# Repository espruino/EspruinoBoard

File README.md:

EspruinoBoard
============

Espruino Hardware Schematics

This repository contains the hardware schematics for the Espruino Boards.

* [Original Espruino Board](http://www.espruino.com/EspruinoBoard) - [see schematics](Original)
* [Espruino Pico Board](http://www.espruino.com/Pico) - [see schematics](Pico)
* [Espruino WiFi Board](http://www.espruino.com/WiFi) - [see schematics](WiFi)
* [Puck.js Board](http://www.espruino.com/Puck.js) - [see schematics](Puck.js)
* [Pixl.js Board](http://www.espruino.com/Pixl.js) - [see schematics](Pixl.js)
* [MDBT42Q Breakout Board](http://www.espruino.com/MDBT42Q) and Eagle Library - [see schematics](MDBT42)

If you want to buy pre-made boards [please support us by buying from here](http://www.espruino.com/Order)

* [Boxes for Espruino Boards](boxes)
* [Fritzing part library](frizting)
* [Bangle.js related parts](Bangle.js)

See the [LICENSE](LICENSE) file for details of the license in this repository.

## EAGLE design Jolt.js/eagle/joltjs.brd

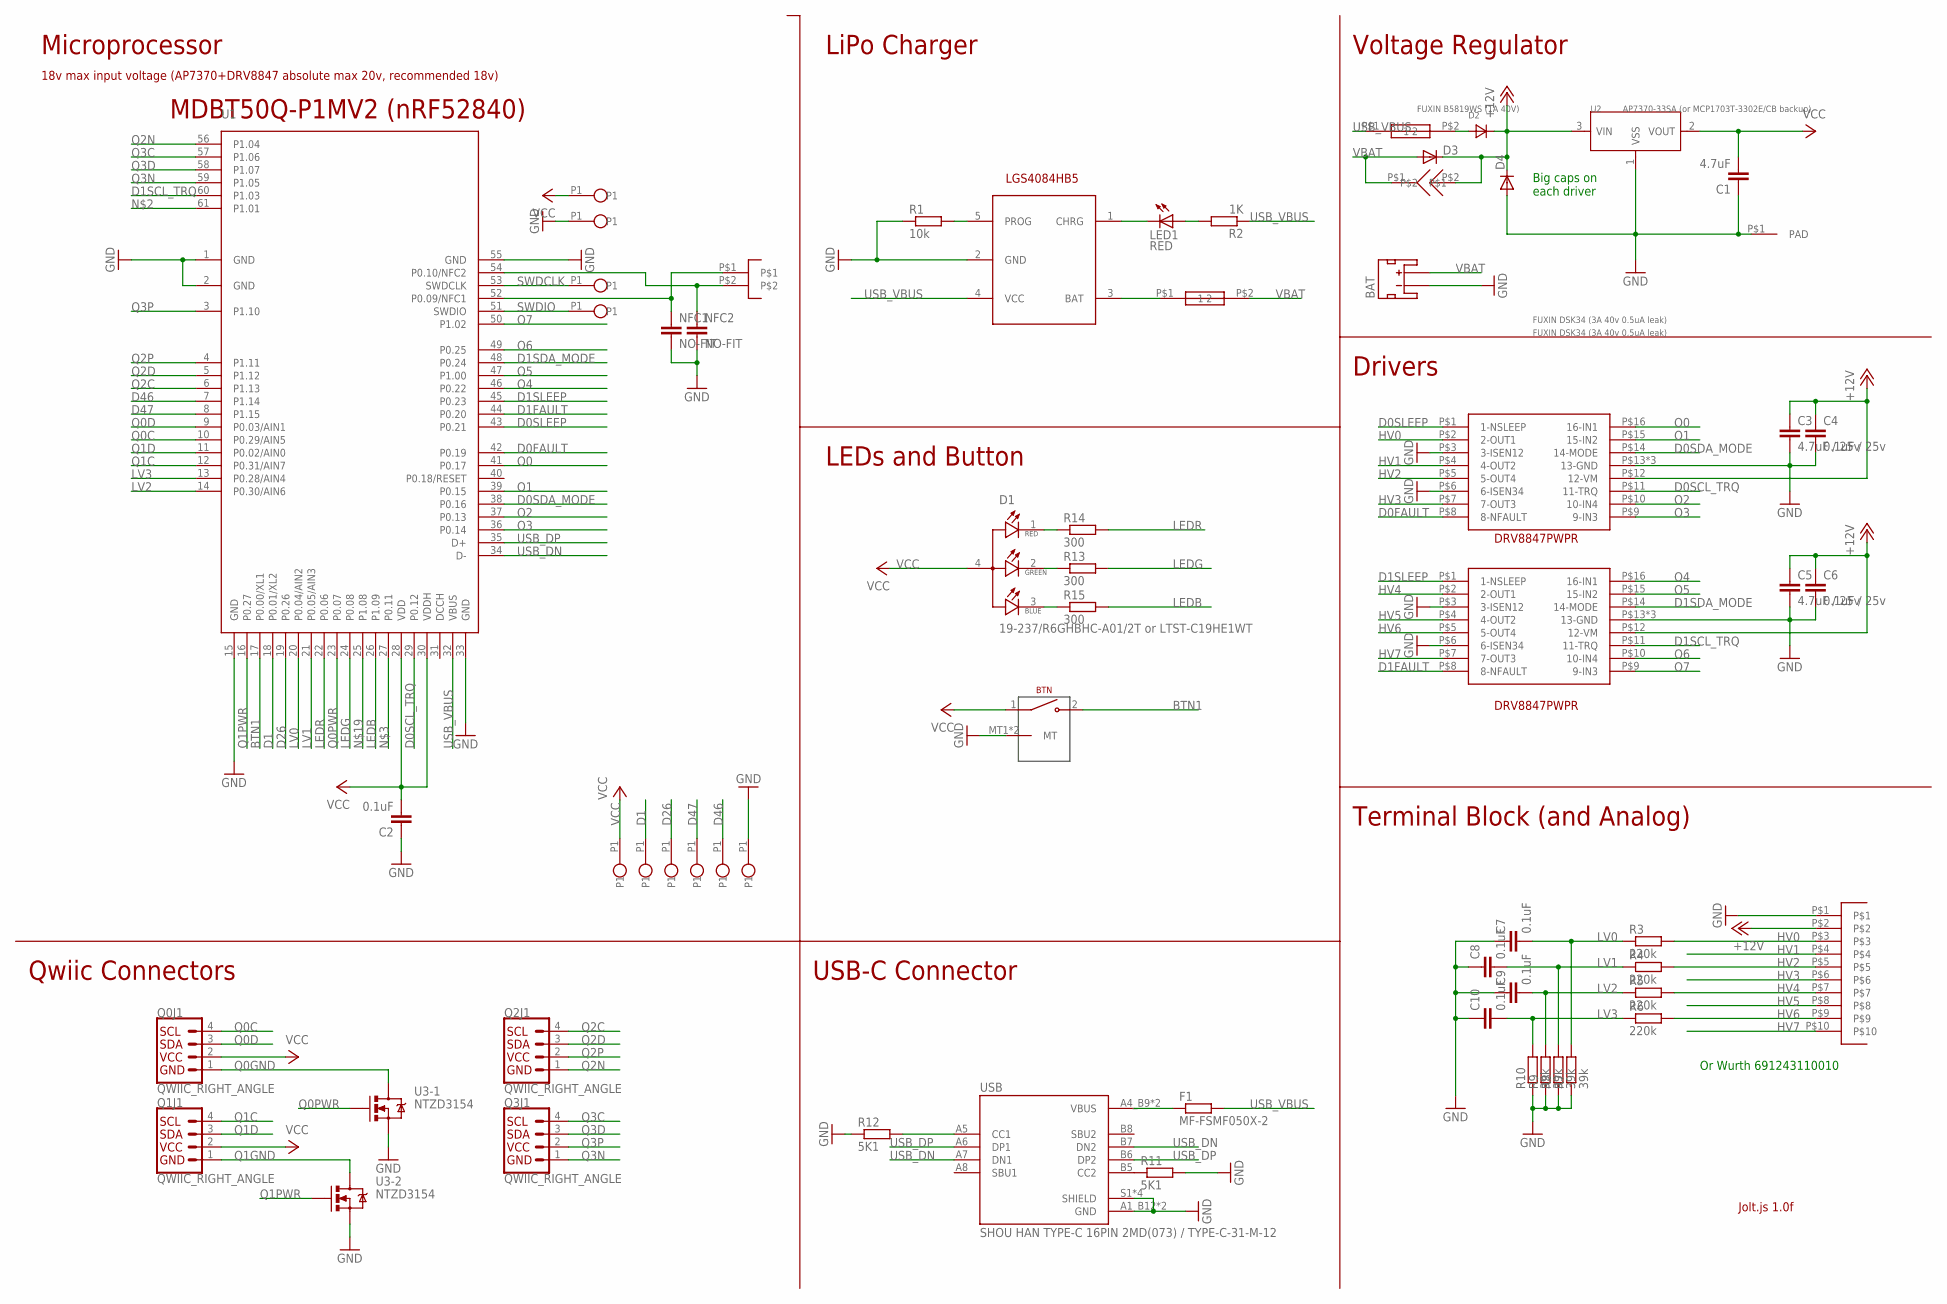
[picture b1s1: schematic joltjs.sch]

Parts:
BAT: C47647 / S2B-PH-SM4-TB; JST-2-SMD
BTN: GT-TC054C; TACT_MEDI_RIGHT_ANGLE
C1: 4.7uF; C0805
C2, C7, C8, C9, C10: 0.1uF; C0603
C3, C5: 4.7uF / 25v; C0805
C4, C6: 0.1uF / 25v; C0603
D1: 19-237/R6GHBHC-A01/2T or LTST-C19HE1WT; LED_19-237/R6GHBHC-A01/2T
D2: FUXIN B5819WS (1A 40V); SOD323
D3, D4: FUXIN DSK34 (3A 40v 0.5uA leak); SOD-123_MINI-SMA
F1: MF-FSMF050X-2; R0603
JUMPER_LIPO_CHG: NO-FIT; WIRELINK2
JUMPER_LIPO_PWR: NO-FIT; SOLDERJUMPER
JUMPER_USB_PWR: NO-FIT; WIRELINK2
LED1: RED; CHIPLED_0603
NFC: PINHEAD-1.27-2X1
NFC1, NFC2: NO-FIT; C0603
Q0, Q1, Q2, Q3: QWIIC_RIGHT_ANGLE; JST04_1MM_RA
R1: 10k; R0603
R2: 1K; R0603
R3, R4, R5, R6: 220k; R0603
R7, R8, R9, R10: 39k; R0603
R11, R12: 5K1; R0603
R13, R14, R15: 300; R0603
SCREWHOLE: MOUNT-M3
SWCK, SWCK2: NO-FIT; SINGLE
SWD: NO-FIT; SINGLE
U1: MDBT50Q-P1MV2; MDBT50
U2: AP7370-33SA (or MCP1703T-3302E/CB backup); SOT23A
U3: NTZD3154; SOT563
U4: LGS4084HB5; SOT23-5
U$5: DORABO DB125-3.5-10P-GN-S; DB125-3.5-XXP
UD1, UD2: DRV8847PWPR
USB: SHOU HAN TYPE-C 16PIN 2MD(073) / TYPE-C-31-M-12; HRO_TYPE-C-31-M-12
VCC, VCC1, VCC2, VCC3, VCC4, VCC5, VCC6: NO-FIT; SINGLE

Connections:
+12V: C3.1, C4.1, C5.1, C6.1, D2.C, D3.C, D4.C, JUMPER_LIPO_PWR.P$2, U2.3 (VIN), U$5.P$2, UD1.P$12 (12-VM), UD2.P$12 (12-VM)
BTN1: BTN.2, U1.17 (P0.00/XL1)
D0FAULT: U1.42 (P0.19), UD1.P$8 (8-NFAULT)
D0SCL_TRQ: U1.29 (P0.12), UD1.P$11 (11-TRQ)
D0SDA_MODE: U1.38 (P0.16), UD1.P$14 (14-MODE)
D0SLEEP: U1.43 (P0.21), UD1.P$1 (1-NSLEEP)
D1: U1.18 (P0.01/XL2), VCC5.P1
D1FAULT: U1.44 (P0.20), UD2.P$8 (8-NFAULT)
D1SCL_TRQ: U1.60 (P1.03), UD2.P$11 (11-TRQ)
D1SDA_MODE: U1.48 (P0.24), UD2.P$14 (14-MODE)
D1SLEEP: U1.45 (P0.23), UD2.P$1 (1-NSLEEP)
D26: U1.19 (P0.26), VCC4.P1
D46: U1.7 (P1.14), VCC2.P1
D47: U1.8 (P1.15), VCC3.P1
GND: BAT.1 (-), BTN.MT1 (MT), BTN.MT2 (MT), C1.1, C2.1, C3.2, C4.2, C5.2, C6.2, C7.1, C8.1, C9.1, C10.1, D4.A, NFC1.2, NFC2.2, R1.1, R7.1, R8.1, R9.1, R10.1, R11.2, R12.1, SCREWHOLE.P$1, SWCK2.P1, U1.1 (GND), U1.2 (GND), U1.15 (GND), U1.33 (GND), U1.55 (GND), U2.1 (VSS), U3.S1 (S), U3.S2 (S), U4.2 (GND), U$5.P$1, UD1.P$3 (3-ISEN12), UD1.P$6 (6-ISEN34), UD1.P$13 (13-GND), UD1.P$17 (13-GND), UD1.P$18 (13-GND), UD2.P$3 (3-ISEN12), UD2.P$6 (6-ISEN34), UD2.P$13 (13-GND), UD2.P$17 (13-GND), UD2.P$18 (13-GND), USB.A1_B12 (GND), USB.B1_A12 (GND), USB.S1 (SHIELD), USB.S2 (SHIELD), USB.S3 (SHIELD), USB.S4 (SHIELD), VCC1.P1
HV0: R3.2, U$5.P$3, UD1.P$2 (2-OUT1)
HV1: U$5.P$4, UD1.P$4 (4-OUT2)
HV2: R4.2, U$5.P$5, UD1.P$5 (5-OUT4)
HV3: U$5.P$6, UD1.P$7 (7-OUT3)
HV4: R5.2, U$5.P$7, UD2.P$2 (2-OUT1)
HV5: U$5.P$8, UD2.P$4 (4-OUT2)
HV6: R6.2, U$5.P$9, UD2.P$5 (5-OUT4)
HV7: U$5.P$10, UD2.P$7 (7-OUT3)
LEDB: R15.2, U1.26 (P1.09)
LEDG: R13.2, U1.24 (P0.08)
LEDR: R14.2, U1.22 (P0.06)
LV0: C7.2, R3.1, R7.2, U1.20 (P0.04/AIN2)
LV1: C8.2, R4.1, R8.2, U1.21 (P0.05/AIN3)
LV2: C9.2, R5.1, R9.2, U1.14 (P0.30/AIN6)
LV3: C10.2, R6.1, R10.2, U1.13 (P0.28/AIN4)
unnamed: LED1.C, U4.1 (CHRG)
unnamed: LED1.A, R2.2
unnamed: JUMPER_LIPO_CHG.P$1 (1), U4.3 (BAT)
unnamed: NFC.P$2, NFC2.1, U1.54 (P0.10/NFC2)
unnamed: D2.A, JUMPER_USB_PWR.P$2 (2)
unnamed: R11.1, USB.B5 (CC2)
unnamed: NFC.P$1, NFC1.1, U1.52 (P0.09/NFC1)
unnamed: R12.2, USB.A5 (CC1)
unnamed: D1.1 (R_C), R14.1
unnamed: D1.2 (G_C), R13.1
unnamed: D1.3 (B_C), R15.1
unnamed: R1.2, U4.5 (PROG)
O0: U1.41 (P0.17), UD1.P$16 (16-IN1)
O1: U1.39 (P0.15), UD1.P$15 (15-IN2)
O2: U1.37 (P0.13), UD1.P$10 (10-IN4)
O3: U1.36 (P0.14), UD1.P$9 (9-IN3)
O4: U1.46 (P0.22), UD2.P$16 (16-IN1)
O5: U1.47 (P1.00), UD2.P$15 (15-IN2)
O6: U1.49 (P0.25), UD2.P$10 (10-IN4)
O7: U1.50 (P1.02), UD2.P$9 (9-IN3)
Q0C: Q0.4, U1.10 (P0.29/AIN5)
Q0D: Q0.3, U1.9 (P0.03/AIN1)
Q0GND: Q0.1, U3.D1 (D)
Q0PWR: U1.23 (P0.07), U3.G1 (G)
Q1C: Q1.4, U1.12 (P0.31/AIN7)
Q1D: Q1.3, U1.11 (P0.02/AIN0)
Q1GND: Q1.1, U3.D2 (D)
Q1PWR: U1.16 (P0.27), U3.G2 (G)
Q2C: Q2.4, U1.6 (P1.13)
Q2D: Q2.3, U1.5 (P1.12)
Q2N: Q2.1, U1.56 (P1.04)
Q2P: Q2.2, U1.4 (P1.11)
Q3C: Q3.4, U1.57 (P1.06)
Q3D: Q3.3, U1.58 (P1.07)
Q3N: Q3.1, U1.59 (P1.05)
Q3P: Q3.2, U1.3 (P1.10)
SWDCLK: SWCK.P1, U1.53 (SWDCLK)
SWDIO: SWD.P1, U1.51 (SWDIO)
USB_DN: U1.34 (D-), USB.A7 (DN1), USB.B7 (DN2)
USB_DP: U1.35 (D+), USB.A6 (DP1), USB.B6 (DP2)
USB_VBUS: F1.2, JUMPER_USB_PWR.P$1 (1), R2.1, U1.32 (VBUS), U4.4 (VCC)
VBAT: BAT.2 (+), D3.A, JUMPER_LIPO_CHG.P$2 (2), JUMPER_LIPO_PWR.P$1
VBUS: F1.1, USB.A4_B9 (VBUS), USB.B4_A9 (VBUS)
VCC: BTN.1, C1.2, C2.2, D1.4 (A), Q0.2, Q1.2, U1.28 (VDD), U1.30 (VDDH), U2.2 (VOUT), VCC.P1, VCC6.P1

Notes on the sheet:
Jolt.js 1.0f
18v max input voltage (AP7370+DRV8847 absolute max 20v, recommended 18v)
DRV8847PWPR
LGS4084HB5
Qwiic Connectors
Microprocessor
MDBT50Q-P1MV2 (nRF52840)
LiPo Charger
LEDs and Button
Voltage Regulator
Drivers
Terminal Block (and Analog)
USB-C Connector
Big caps on each driver
Or Wurth 691243110010

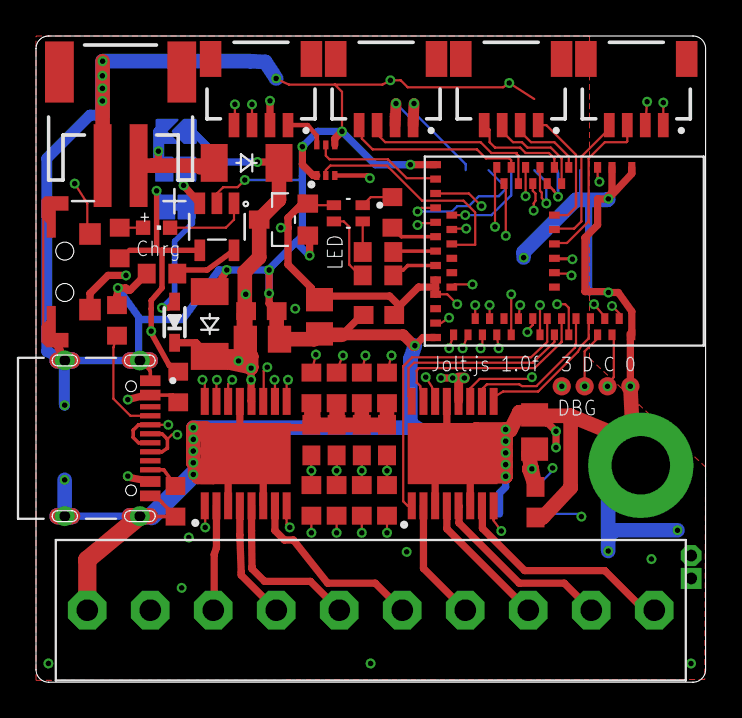
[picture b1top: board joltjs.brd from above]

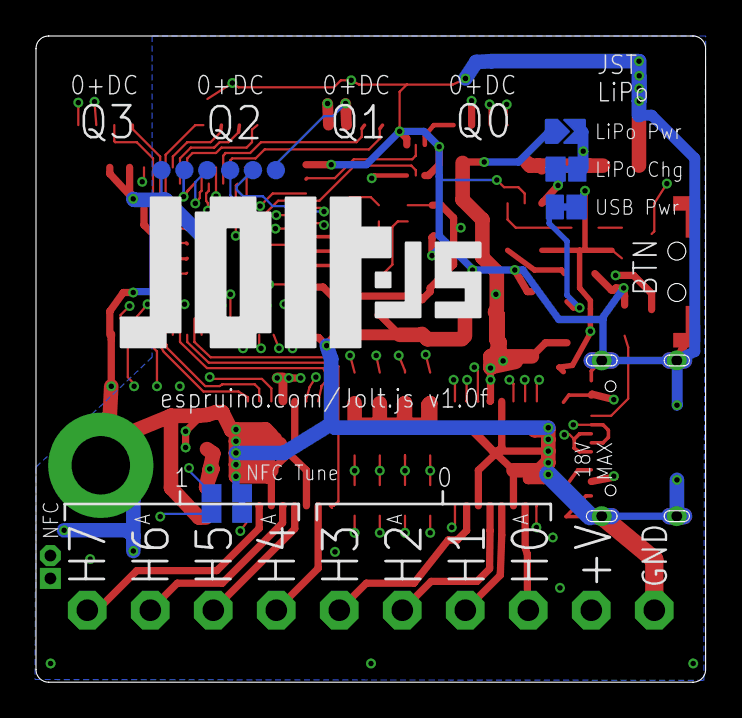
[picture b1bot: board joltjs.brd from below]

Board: 4 copper layers, 37.2 x 35.9 mm, 62 parts (11 on the bottom side), 74 nets.

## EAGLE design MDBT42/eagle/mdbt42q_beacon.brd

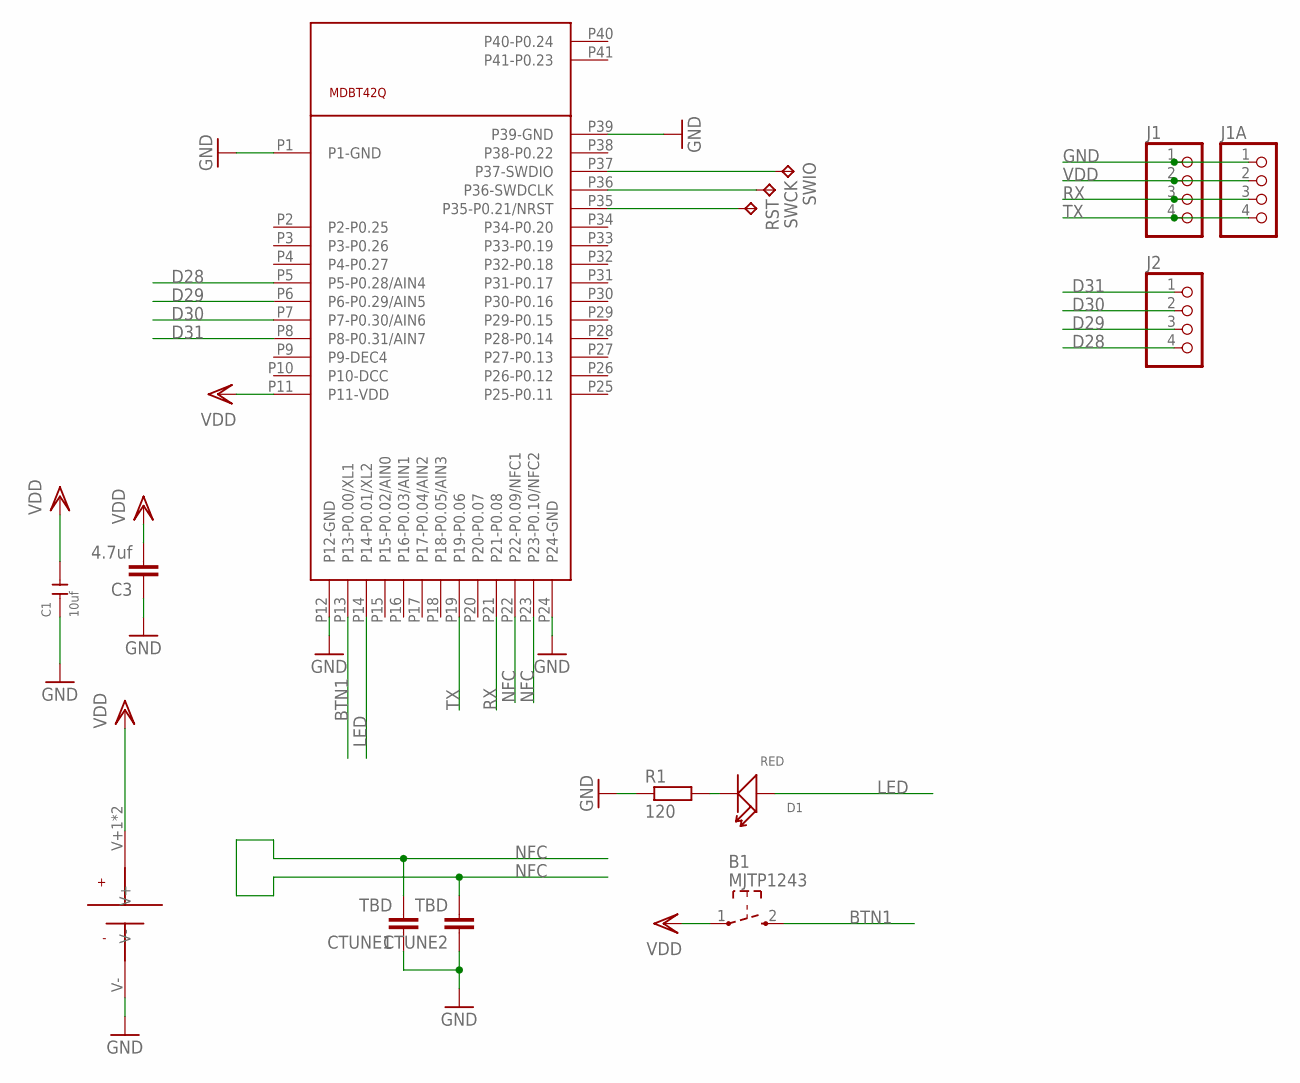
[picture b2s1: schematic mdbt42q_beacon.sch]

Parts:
B1: MJTP1243
C1: 10uf; C0805
C3: 4.7uf; C0603
CTUNE1, CTUNE2: TBD; C0603
D1: RED; LED-0603
J1, J2: PINHD-1X04_2.54-S; 1X04-S
J1A: PINHD-1X04; 1X04M2
J8: KEYSTONE-3003
R1: 120; R0603
RST: TPTP15R; TP15R
SWCK: TPTP15R; TP15R
SWIO: TPTP15R; TP15R
U1: MDBT42Q; MDBT40

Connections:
BTN1: B1.2 (3), U1.P13 (P13-P0.00/XL1)
D28: J2.4, U1.P5 (P5-P0.28/AIN4)
D29: J2.3, U1.P6 (P6-P0.29/AIN5)
D30: J2.2, U1.P7 (P7-P0.30/AIN6)
D31: J2.1, U1.P8 (P8-P0.31/AIN7)
GND: C1.1, C3.1, CTUNE1.1, CTUNE2.1, J1.1, J1A.1, J8.V-, R1.1, U1.P1 (P1-GND), U1.P12 (P12-GND), U1.P24 (P24-GND), U1.P39 (P39-GND)
LED: D1.+, U1.P14 (P14-P0.01/XL2)
unnamed: D1.-, R1.2
unnamed: SWCK.TP, U1.P36 (P36-SWDCLK)
unnamed: SWIO.TP, U1.P37 (P37-SWDIO)
unnamed: RST.TP, U1.P35 (P35-P0.21/NRST)
NFC: CTUNE1.2, CTUNE2.2, U1.P22 (P22-P0.09/NFC1), U1.P23 (P23-P0.10/NFC2)
RX: J1.3, J1A.3, U1.P21 (P21-P0.08)
TX: J1.4, J1A.4, U1.P19 (P19-P0.06)
VDD: B1.1, C1.2, C3.2, J1.2, J1A.2, J8.V+1 (V+), J8.V+2 (V+), U1.P11 (P11-VDD)

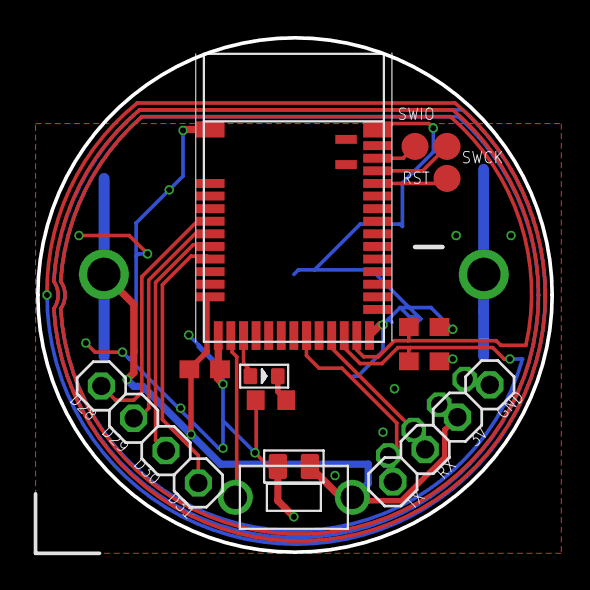
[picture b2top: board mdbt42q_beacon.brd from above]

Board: 2 copper layers, 28.6 x 28.6 mm, 15 parts (1 on the bottom side), 15 nets.

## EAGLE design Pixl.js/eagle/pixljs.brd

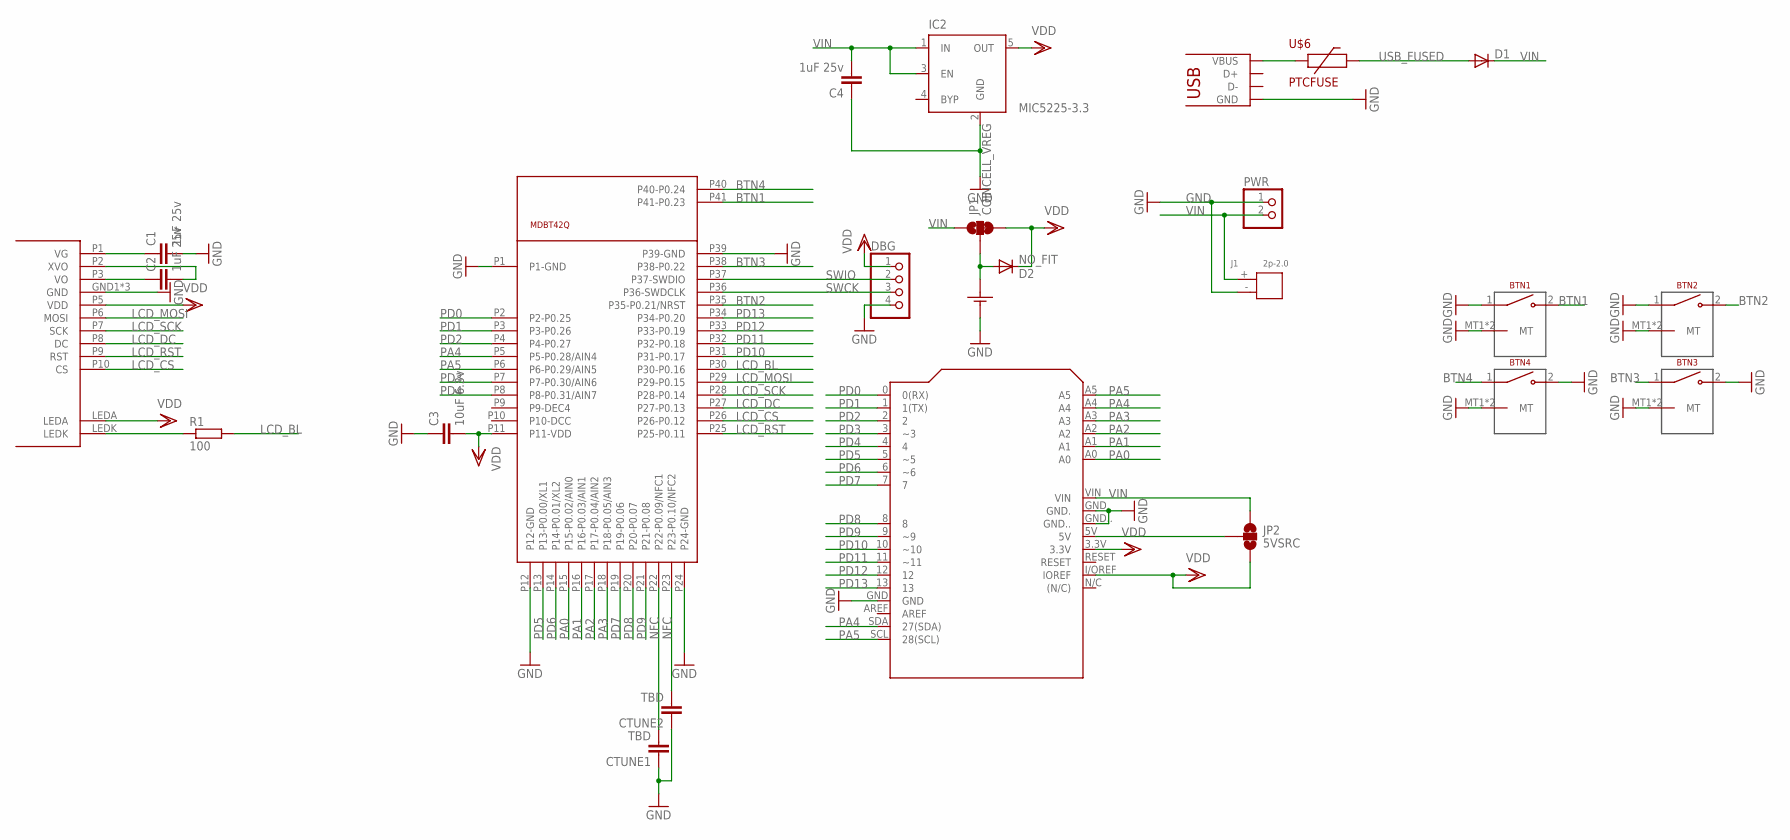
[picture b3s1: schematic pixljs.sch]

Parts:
BTN1, BTN2, BTN3, BTN4: TACT_MINI_RIGHT_ANGLEMEDI; TACT_MEDI_RIGHT_ANGLE
C1, C2, C4: 1uF 25v; C0603K
C3: 10uF 6.3v; C0603K
CTUNE1, CTUNE2: TBD; C0603K
D1: DIODE-SOD323-W; SOD323-W
D2: NO_FIT; SOD323-W
DBG: PINHD-1X04_2.54-S; 1X04-S
IC2: MIC5225-3.3; SOT23-5
J1: 2p-2.0; H2-2.0-6X4.5MM
JP1: COINCELL_VREG; SMT-JUMPER_3_1-NC_TRACE_NO-SILK
JP2: 5VSRC; SMT-JUMPER_3_NO_NO-SILK
PWR: PINHD-1X02_2.54-S; 1X02-S
R1: 100; R0603
U$1: JHD12864; JHD12864-G176BSW
U$2: MDBT42Q; MDBT40
U$3: CR2032-SMD
U$4: ARDUINO
U$5: USB-MICROB
U$6: PTCFUSE; R1210

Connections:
BTN1: BTN1.2, U$2.P41 (P41-P0.23)
BTN2: BTN2.2, U$2.P35 (P35-P0.21/NRST)
BTN3: BTN3.1, U$2.P38 (P38-P0.22)
BTN4: BTN4.1, U$2.P40 (P40-P0.24)
GND: BTN1.1, BTN1.MT1 (MT), BTN1.MT2 (MT), BTN2.1, BTN2.MT1 (MT), BTN2.MT2 (MT), BTN3.2, BTN3.MT1 (MT), BTN3.MT2 (MT), BTN4.2, BTN4.MT1 (MT), BTN4.MT2 (MT), C1.2, C3.1, C4.1, CTUNE1.1, CTUNE2.1, DBG.4, IC2.2 (GND), J1.-, PWR.1, U$1.GND1 (GND), U$1.GND2 (GND), U$1.P4 (GND), U$2.P1 (P1-GND), U$2.P12 (P12-GND), U$2.P24 (P24-GND), U$2.P39 (P39-GND), U$3.NEG (-), U$4.GND, U$4.GND., U$4.GND.., U$5.GND, U$5.MT1 (GND), U$5.MT2 (GND), U$5.P$1 (GND), U$5.P$2 (GND), U$5.P$3 (GND), U$5.P$4 (GND)
LCD_BL: R1.2, U$2.P30 (P30-P0.16)
LCD_CS: U$1.P10 (CS), U$2.P26 (P26-P0.12)
LCD_DC: U$1.P8 (DC), U$2.P27 (P27-P0.13)
LCD_MOSI: U$1.P6 (MOSI), U$2.P29 (P29-P0.15)
LCD_RST: U$1.P9 (RST), U$2.P25 (P25-P0.11)
LCD_SCK: U$1.P7 (SCK), U$2.P28 (P28-P0.14)
unnamed: D2.A, JP1.2, U$3.POS1 (+), U$3.POS2 (+)
unnamed: C2.1, U$1.P3 (VO)
unnamed: C2.2, U$1.P2 (XVO)
unnamed: C1.1, U$1.P1 (VG)
unnamed: R1.1, U$1.LEDK
unnamed: U$5.VBUS, U$6.1
unnamed: JP2.2, U$4.5V
NFC: CTUNE1.2, CTUNE2.2, U$2.P22 (P22-P0.09/NFC1), U$2.P23 (P23-P0.10/NFC2)
PA0: U$2.P15 (P15-P0.02/AIN0), U$4.A0
PA1: U$2.P16 (P16-P0.03/AIN1), U$4.A1
PA2: U$2.P17 (P17-P0.04/AIN2), U$4.A2
PA3: U$2.P18 (P18-P0.05/AIN3), U$4.A3
PA4: U$2.P5 (P5-P0.28/AIN4), U$4.A4, U$4.SDA (27(SDA))
PA5: U$2.P6 (P6-P0.29/AIN5), U$4.A5, U$4.SCL (28(SCL))
PD0: U$2.P2 (P2-P0.25), U$4.0 (0(RX))
PD1: U$2.P3 (P3-P0.26), U$4.1 (1(TX))
PD2: U$2.P4 (P4-P0.27), U$4.2
PD3: U$2.P7 (P7-P0.30/AIN6), U$4.3 (~3)
PD4: U$2.P8 (P8-P0.31/AIN7), U$4.4
PD5: U$2.P13 (P13-P0.00/XL1), U$4.5 (~5)
PD6: U$2.P14 (P14-P0.01/XL2), U$4.6 (~6)
PD7: U$2.P19 (P19-P0.06), U$4.7
PD8: U$2.P20 (P20-P0.07), U$4.8
PD9: U$2.P21 (P21-P0.08), U$4.9 (~9)
PD10: U$2.P31 (P31-P0.17), U$4.10 (~10)
PD11: U$2.P32 (P32-P0.18), U$4.11 (~11)
PD12: U$2.P33 (P33-P0.19), U$4.12
PD13: U$2.P34 (P34-P0.20), U$4.13
SWCK: DBG.3, U$2.P36 (P36-SWDCLK)
SWIO: DBG.2, U$2.P37 (P37-SWDIO)
USB_FUSED: D1.A, U$6.2
VDD: C3.2, D2.C, DBG.1, IC2.5 (OUT), JP1.3, JP2.3, U$1.LEDA, U$1.P5 (VDD), U$2.P11 (P11-VDD), U$4.3.3V, U$4.I/OREF (IOREF)
VIN: C4.2, D1.C, IC2.1 (IN), IC2.3 (EN), J1.+, JP1.1, JP2.1, PWR.2, U$4.VIN

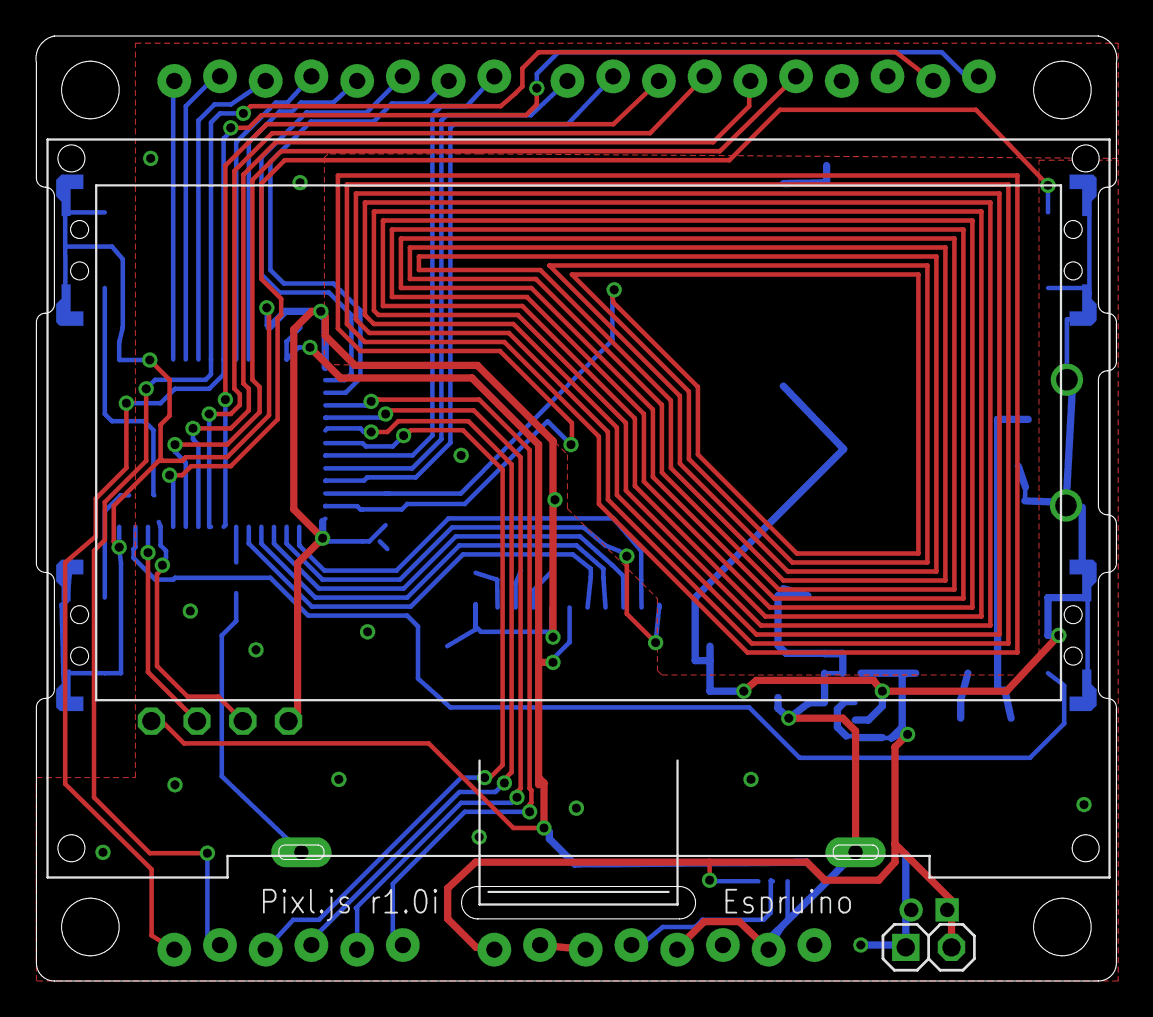
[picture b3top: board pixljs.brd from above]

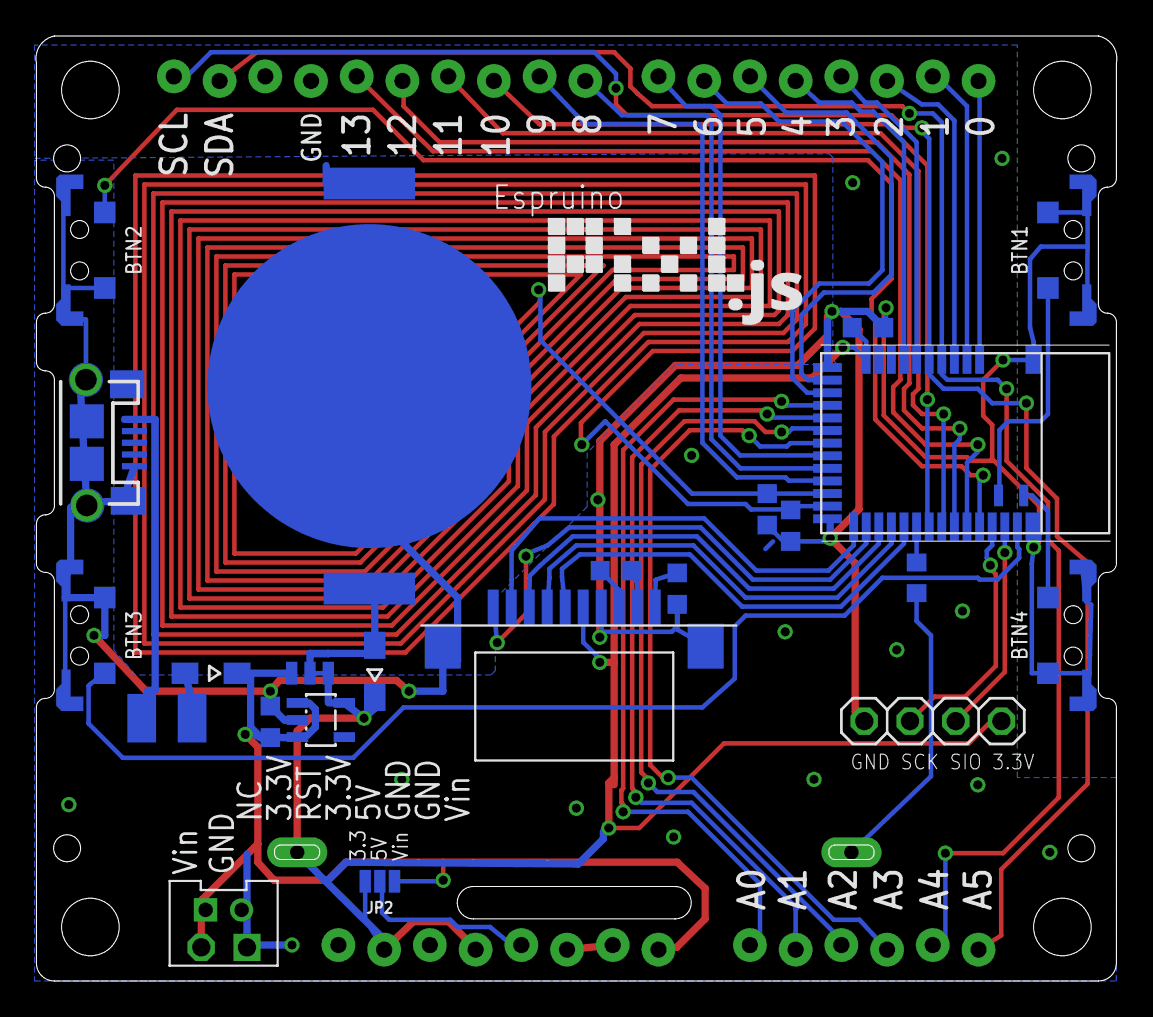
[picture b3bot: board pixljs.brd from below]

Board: 2 copper layers, 60.0 x 52.5 mm, 29 parts (23 on the bottom side), 44 nets.

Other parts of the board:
U$7, U$8, U$9, U$10: M3

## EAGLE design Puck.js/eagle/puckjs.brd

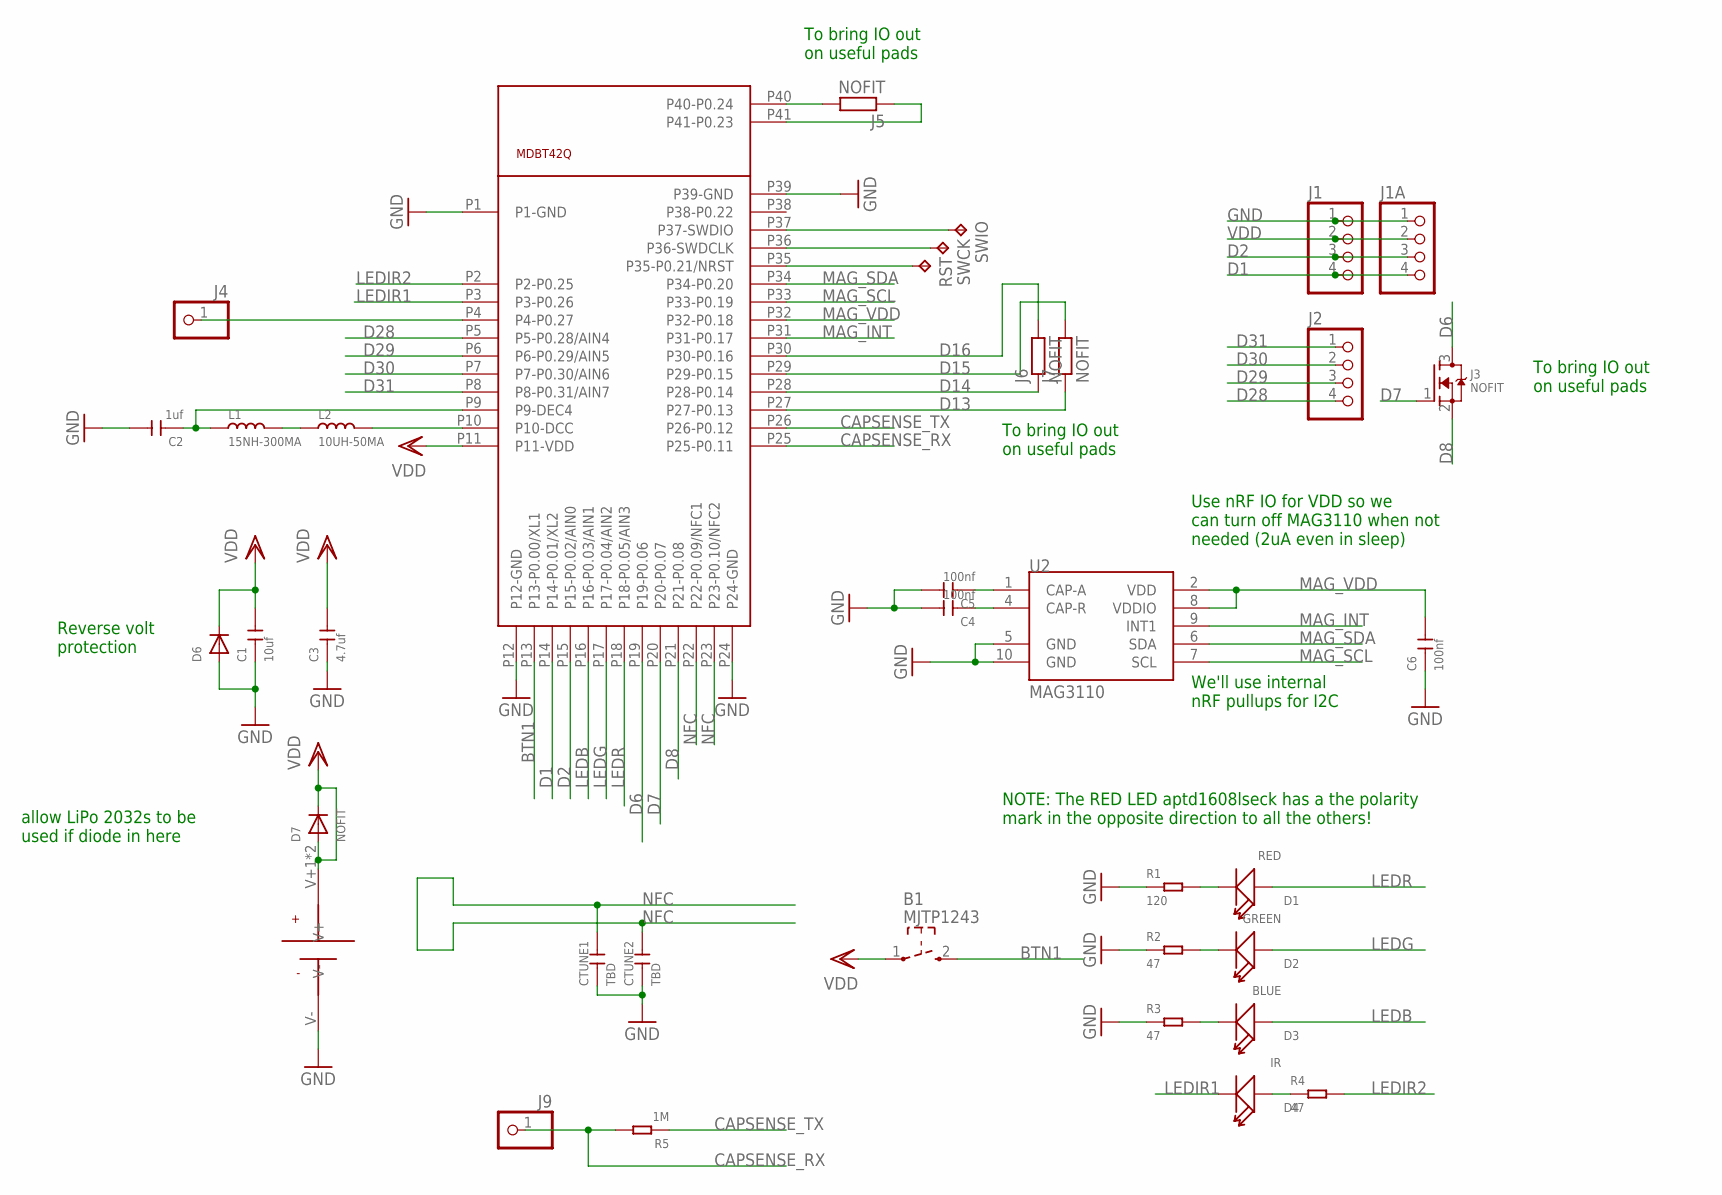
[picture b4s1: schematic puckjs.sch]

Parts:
B1: MJTP1243
C1: 10uf; C0805
C2: 1uf; C0402
C3: 4.7uf; C0402
C4, C5, C6: 100nf; C0402
CTUNE1, CTUNE2: TBD; C0402
D1: RED; LED-0603
D2: GREEN; LED-0603
D3: BLUE; LED-0603
D4: IR; LED-0603
D6: DIODESOD-523; SOD-523
D7: NOFIT; SOD-523
J1, J2: PINHD-1X04_2.54-S; 1X04-S
J1A: PINHD-1X04; 1X04M2
J3: NOFIT; SOT23
J4, J9: PINHD-1X1; 1X01
J5: NOFIT; R1206
J6, J7: NOFIT; R0603
J8: KEYSTONE-3003
L1: 15NH-300MA; L0402
L2: 10UH-50MA; L0603
R1: 120; R0402
R2, R3, R4: 47; R0402
R5: 1M; R0402
RST: TPTP15R; TP15R
SWCK: TPTP15R; TP15R
SWIO: TPTP15R; TP15R
U1: MDBT42Q; MDBT40
U2: MAG3110; DFN-10

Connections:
BTN1: B1.2 (3), U1.P13 (P13-P0.00/XL1)
CAPSENSE_RX: J9.1, R5.2, U1.P25 (P25-P0.11)
CAPSENSE_TX: R5.1, U1.P26 (P26-P0.12)
D1: J1.4, J1A.4, U1.P14 (P14-P0.01/XL2)
D2: J1.3, J1A.3, U1.P15 (P15-P0.02/AIN0)
D6: J3.3 (D), U1.P19 (P19-P0.06)
D7: J3.1 (G), U1.P20 (P20-P0.07)
D8: J3.2 (S), U1.P21 (P21-P0.08)
D13: J7.1, U1.P27 (P27-P0.13)
D14: J6.1, U1.P28 (P28-P0.14)
D15: J7.2, U1.P29 (P29-P0.15)
D16: J6.2, U1.P30 (P30-P0.16)
D28: J2.4, U1.P5 (P5-P0.28/AIN4)
D29: J2.3, U1.P6 (P6-P0.29/AIN5)
D30: J2.2, U1.P7 (P7-P0.30/AIN6)
D31: J2.1, U1.P8 (P8-P0.31/AIN7)
GND: C1.1, C2.2, C3.1, C4.2, C5.2, C6.1, CTUNE1.1, CTUNE2.1, D6.A, J1.1, J1A.1, J8.V-, R1.1, R2.1, R3.1, U1.P1 (P1-GND), U1.P12 (P12-GND), U1.P24 (P24-GND), U1.P39 (P39-GND), U2.5 (GND), U2.10 (GND)
LEDB: D3.+, U1.P16 (P16-P0.03/AIN1)
LEDG: D2.+, U1.P17 (P17-P0.04/AIN2)
LEDIR1: D4.-, U1.P3 (P3-P0.26)
LEDIR2: R4.2, U1.P2 (P2-P0.25)
LEDR: D1.+, U1.P18 (P18-P0.05/AIN3)
MAG_INT: U1.P31 (P31-P0.17), U2.9 (INT1)
MAG_SCL: U1.P33 (P33-P0.19), U2.7 (SCL)
MAG_SDA: U1.P34 (P34-P0.20), U2.6 (SDA)
MAG_VDD: C6.2, U1.P32 (P32-P0.18), U2.2 (VDD), U2.8 (VDDIO)
unnamed: D1.-, R1.2
unnamed: D2.-, R2.2
unnamed: D3.-, R3.2
unnamed: J4.1, U1.P4 (P4-P0.27)
unnamed: SWCK.TP, U1.P36 (P36-SWDCLK)
unnamed: SWIO.TP, U1.P37 (P37-SWDIO)
unnamed: J5.2, U1.P40 (P40-P0.24)
unnamed: J5.1, U1.P41 (P41-P0.23)
unnamed: D4.+, R4.1
unnamed: C2.1, L1.1, U1.P9 (P9-DEC4)
unnamed: L1.2, L2.1
unnamed: C5.1, U2.1 (CAP-A)
unnamed: L2.2, U1.P10 (P10-DCC)
unnamed: RST.TP, U1.P35 (P35-P0.21/NRST)
unnamed: C4.1, U2.4 (CAP-R)
NFC: CTUNE1.2, CTUNE2.2, U1.P22 (P22-P0.09/NFC1), U1.P23 (P23-P0.10/NFC2)
VDD: B1.1, C1.2, C3.2, D6.K (C), D7.A, D7.K (C), J1.2, J1A.2, J8.V+1 (V+), J8.V+2 (V+), U1.P11 (P11-VDD)

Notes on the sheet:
We'll use internal nRF pullups for I2C
Use nRF IO for VDD so we can turn off MAG3110 when not needed (2uA even in sleep)
To bring IO out on useful pads
allow LiPo 2032s to be used if diode in here
Reverse volt protection
NOTE: The RED LED aptd1608lseck has a the polarity mark in the opposite direction to all the others!

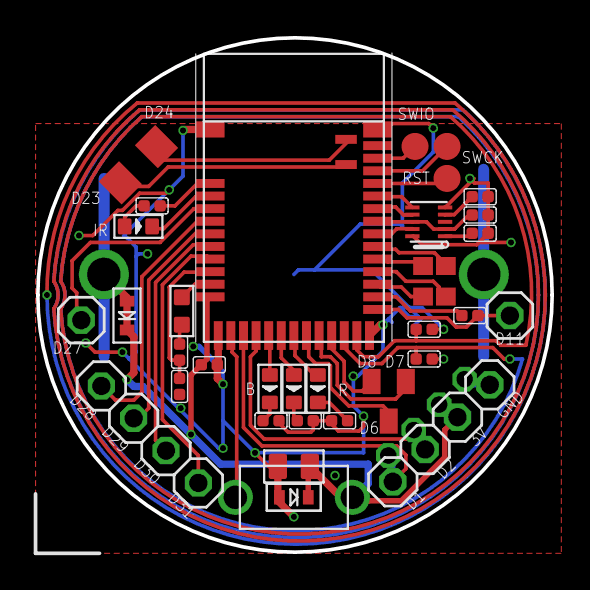
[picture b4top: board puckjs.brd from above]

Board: 2 copper layers, 28.6 x 28.6 mm, 37 parts (1 on the bottom side), 43 nets.

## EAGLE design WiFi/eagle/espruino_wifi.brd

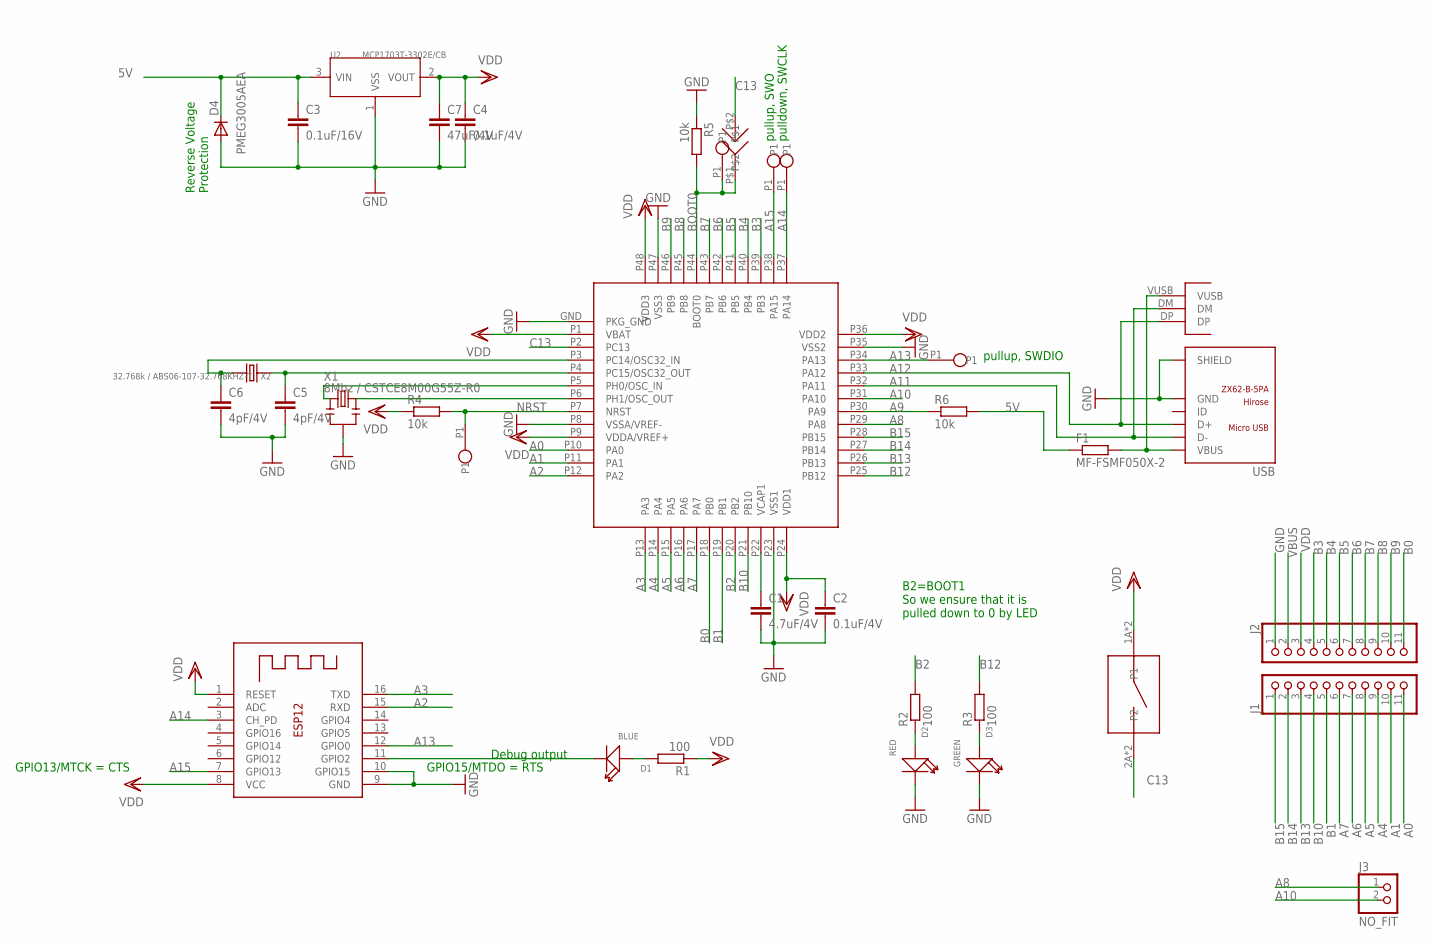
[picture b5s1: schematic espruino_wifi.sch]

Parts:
B1: KMR421NG
C1: 4.7uF/4V; C0402
C2, C4: 0.1uF/4V; C0402
C3: 0.1uF/16V; C0402
C5, C6: 4pF/4V; C0402
C7: 47uF/4V; C1210
D1: BLUE; LED-0402
D2: RED; LED-0402
D3: GREEN; LED-0402
D4: PMEG3005AEA; SOD323-W
F1: MF-FSMF050X-2; R0603
J1, J2: PINHD-1X11_2.54-S; 1X11-S
J3: NO_FIT; 1X02-S
J4: NO_FIT; SOLDERJUMPER
PBOOT0: NO_FIT; SINGLE
PNRST: NO_FIT; SINGLE
PSWCLK: NO_FIT; SINGLE
PSWDIO: NO_FIT; SINGLE
PSWO: NO_FIT; SINGLE
PUSB: NO_FIT; USB
R1, R2, R3: 100; R0402
R4, R5, R6: 10k; R0402
U1: STM32F411CEU6; UFQFPN48
U2: MCP1703T-3302E/CB; SOT23
U3: ESP-12
USB: ZX62-B-5PA; MICRO-USB5+6P-SMD-0.65-AB
X1: 8Mhz / CSTCE8M00G55Z-R0; 3P-SMD-3.6X1.3
X2: 32.768k / ABS06-107-32.768KHZ-T; 2P-SMD-2.05X1.2

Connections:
5V: C3.1, D4.C, F1.1, R6.2, U2.3 (VIN)
A0: J1.11, U1.P10 (PA0)
A1: J1.10, U1.P11 (PA1)
A2: U1.P12 (PA2), U3.15 (RXD)
A3: U1.P13 (PA3), U3.16 (TXD)
A4: J1.9, U1.P14 (PA4)
A5: J1.8, U1.P15 (PA5)
A6: J1.7, U1.P16 (PA6)
A7: J1.6, U1.P17 (PA7)
A8: J3.1, U1.P29 (PA8)
A9: R6.1, U1.P30 (PA9)
A10: J3.2, U1.P31 (PA10)
A11: PUSB.DM, U1.P32 (PA11), USB.2 (D-)
A12: PUSB.DP, U1.P33 (PA12), USB.3 (D+)
A13: PSWDIO.P1, U1.P34 (PA13), U3.12 (GPIO0)
A14: PSWCLK.P1, U1.P37 (PA14), U3.3 (CH_PD)
A15: PSWO.P1, U1.P38 (PA15), U3.7 (GPIO13)
B0: J2.11, U1.P18 (PB0)
B1: J1.5, U1.P19 (PB1)
B2: R2.2, U1.P20 (PB2)
B3: J2.4, U1.P39 (PB3)
B4: J2.5, U1.P40 (PB4)
B5: J2.6, U1.P41 (PB5)
B6: J2.7, U1.P42 (PB6)
B7: J2.8, U1.P43 (PB7)
B8: J2.9, U1.P45 (PB8)
B9: J2.10, U1.P46 (PB9)
B10: J1.4, U1.P21 (PB10)
B12: R3.2, U1.P25 (PB12)
B13: J1.3, U1.P26 (PB13)
B14: J1.2, U1.P27 (PB14)
B15: J1.1, U1.P28 (PB15)
BOOT0: J4.P$1, PBOOT0.P1, R5.2, U1.P44 (BOOT0)
C13: B1.2A (P2), B1.2B (P2), J4.P$2, U1.P2 (PC13)
GND: C1.3 (2), C2.3 (2), C3.3 (2), C4.3 (2), C5.3 (2), C6.3 (2), C7.2, D2.-, D3.-, D4.A, J2.1, R5.1, U1.GND (PKG_GND), U1.P8 (VSSA/VREF-), U1.P23 (VSS1), U1.P35 (VSS2), U1.P47 (VSS3), U2.1 (VSS), U3.9 (GND), U3.10 (GPIO15), USB.5 (GND), USB.P1 (SHIELD), USB.P2 (SHIELD), USB.P3 (SHIELD), USB.P4 (SHIELD), USB.P5 (SHIELD), USB.P6 (SHIELD), X1.2
unnamed: C5.1, U1.P4 (PC15/OSC32_OUT), X2.1
unnamed: C6.1, U1.P3 (PC14/OSC32_IN), X2.2
unnamed: U1.P5 (PH0/OSC_IN), X1.1
unnamed: U1.P6 (PH1/OSC_OUT), X1.3
unnamed: D2.+, R2.1
unnamed: D3.+, R3.1
unnamed: D1.+, R1.2
unnamed: D1.-, U3.11 (GPIO2)
unnamed: C1.1, U1.P22 (VCAP1)
NRST: PNRST.P1, R4.2, U1.P7 (NRST)
VBUS: F1.2, J2.2, PUSB.VUSB, USB.1 (VBUS)
VDD: B1.1A (P1), B1.1B (P1), C2.1, C4.1, C7.1, J2.3, R1.1, R4.1, U1.P1 (VBAT), U1.P9 (VDDA/VREF+), U1.P24 (VDD1), U1.P36 (VDD2), U1.P48 (VDD3), U2.2 (VOUT), U3.1 (RESET), U3.8 (VCC)

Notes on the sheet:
B2=BOOT1 So we ensure that it is pulled down to 0 by LED
Debug output
pulldown, SWCLK
pullup, SWO
pullup, SWDIO
GPIO13/MTCK = CTS
GPIO15/MTDO = RTS
Reverse Voltage Protection

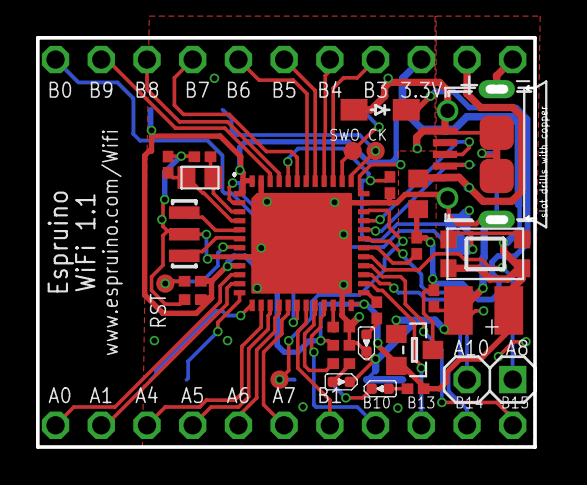
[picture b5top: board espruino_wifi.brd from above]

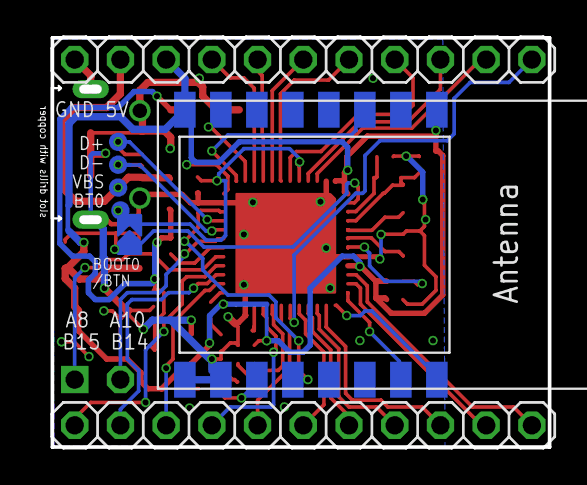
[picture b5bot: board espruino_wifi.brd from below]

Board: 2 copper layers, 27.6 x 22.7 mm, 35 parts (6 on the bottom side), 47 nets.

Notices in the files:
parts and their libraries:
SparkFun-Connectors: Licensing: Creative Commons ShareAlike 4.0 International - https://creativecommons.org/licenses/by-sa/4.0
pimoroni: Licensing: CC v3.0 Share-Alike You are welcome to use this library for commercial purposes.
